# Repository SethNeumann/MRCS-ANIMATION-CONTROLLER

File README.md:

# REPO NAME: MRCS-ANIMATION-CONTROLLER
## License: Creative Commons Attribution-NonCommercial-ShareAlike

MRCS-ANIMATION-CONTROLLER

Intial use of this board is to support an animated fork lift which follows a chain with a magnet below the layout. The fork lift stops at various stations under control of diverters operated by servos. There is an on/off switch, an input for a human presence sensor, a hall effect sensore to home the chain and outputs for status LEDs.

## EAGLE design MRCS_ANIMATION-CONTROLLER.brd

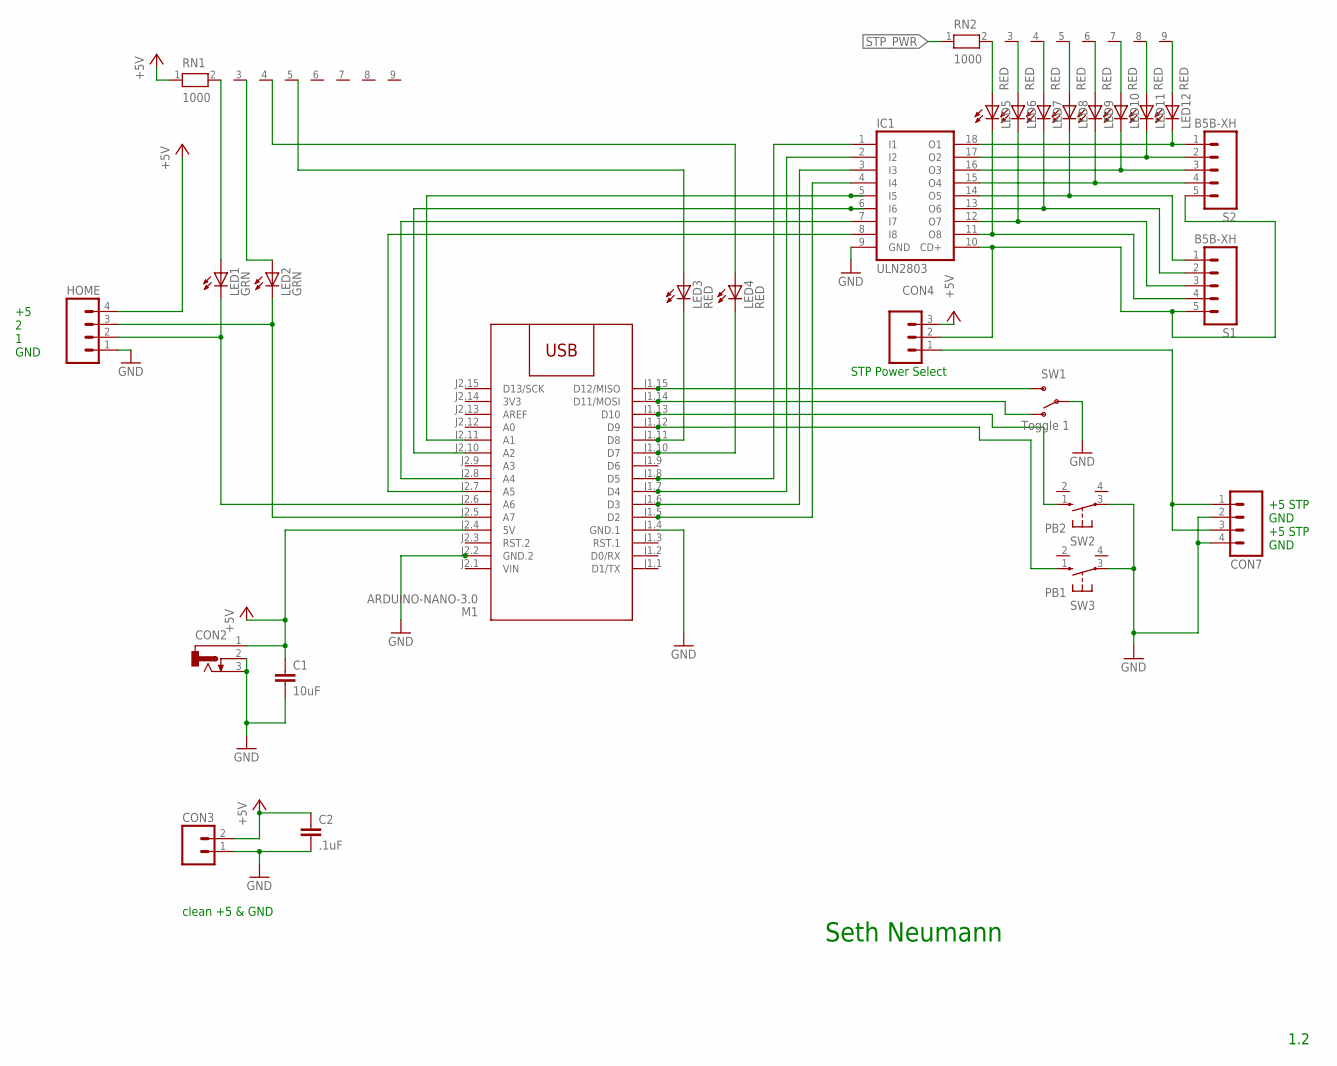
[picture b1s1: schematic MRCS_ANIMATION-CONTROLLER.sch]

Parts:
C1: 10uF; C5B3
C2: .1uF; C5B3
CON2: CONNECTOR-DC-POWER-RA; DCJ0202
CON3: CONNECTOR-M02350-LOCK; 1751248
CON4: CONNECTOR-M03254-LOCK; 3POL254
CON7: CONNECTOR-M04SCREW_LOCK; SCREWTERMINAL-3.5MM-4_LOCK
HOME: CONNECTOR-M04LOCK; 1X04_LOCK
IC1: ULN2803; DIL18
LED1, LED2: GRN; LED3MM
LED3, LED4, LED5, LED6, LED7, LED8, LED9, LED10, LED11, LED12: RED; LED3MM
M1: ARDUINO-NANO-3.0
RN1, RN2: 1000; RN-9
S1, S2: B5B-XH; 1X05_LOCK
SW1: Toggle 1; SWITCH-SPDT-508
SW2: PB2; 4P-PTH-6.0X6.0X5.0H
SW3: PB1; 4P-PTH-6.0X6.0X5.0H

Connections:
3V3: M1.J2.14 (3V3)
+5V: C1.1, C2.1, CON2.1, CON3.2 (B), CON4.3, HOME.4, M1.J2.4 (5V), RN1.1
GND: C1.2, C2.2, CON2.2, CON2.3, CON3.1 (A), CON7.2, CON7.4, HOME.1, IC1.9 (GND), M1.J1.4 (GND.1), M1.J2.2 (GND.2), SW1.2, SW2.3, SW3.3
unnamed: IC1.18 (O1), LED12.K (C), S2.1
unnamed: M1.J1.15 (D12/MISO), SW1.3 (S)
unnamed: M1.J1.14 (D11/MOSI), SW1.1 (O)
unnamed: M1.J1.13 (D10), SW2.1 (S)
unnamed: M1.J1.12 (D9), SW3.1 (S)
unnamed: LED3.K (C), M1.J1.11 (D8)
unnamed: LED4.K (C), M1.J1.10 (D7)
unnamed: LED3.A, RN1.5
unnamed: LED4.A, RN1.4
unnamed: LED2.A, RN1.3
unnamed: IC1.1 (I1), M1.J1.8 (D5)
unnamed: IC1.2 (I2), M1.J1.7 (D4)
unnamed: IC1.3 (I3), M1.J1.6 (D3)
unnamed: IC1.4 (I4), M1.J1.5 (D2)
unnamed: IC1.17 (O2), LED11.K (C), S2.2
unnamed: IC1.16 (O3), LED10.K (C), S2.3
unnamed: IC1.15 (O4), LED9.K (C), S2.4
unnamed: LED9.A, RN2.6
unnamed: HOME.3, LED2.K (C), M1.J2.5 (A7)
unnamed: LED10.A, RN2.7
unnamed: LED11.A, RN2.8
unnamed: LED12.A, RN2.9
unnamed: IC1.5 (I5), M1.J2.11 (A1)
unnamed: IC1.6 (I6), M1.J2.10 (A2)
unnamed: IC1.7 (I7), M1.J2.8 (A4)
unnamed: IC1.8 (I8), M1.J2.7 (A5)
unnamed: LED5.A, RN2.2
unnamed: CON4.1, CON7.1, CON7.3
unnamed: HOME.2, LED1.K (C), M1.J2.6 (A6)
unnamed: LED1.A, RN1.2
unnamed: LED6.A, RN2.3
unnamed: IC1.14 (O5), LED8.K (C), S1.1
unnamed: IC1.13 (O6), LED7.K (C), S1.2
unnamed: IC1.12 (O7), LED6.K (C), S1.3
unnamed: IC1.11 (O8), LED5.K (C), S1.4
unnamed: LED7.A, RN2.4
unnamed: LED8.A, RN2.5
STP_PWR: CON4.2, IC1.10 (CD+), RN2.1, S1.5, S2.5
VIN: M1.J2.1 (VIN)

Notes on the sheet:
Seth Neumann
1.2
clean +5 & GND
+5 STP GND +5 STP GND
STP Power Select
+5 2 1 GND

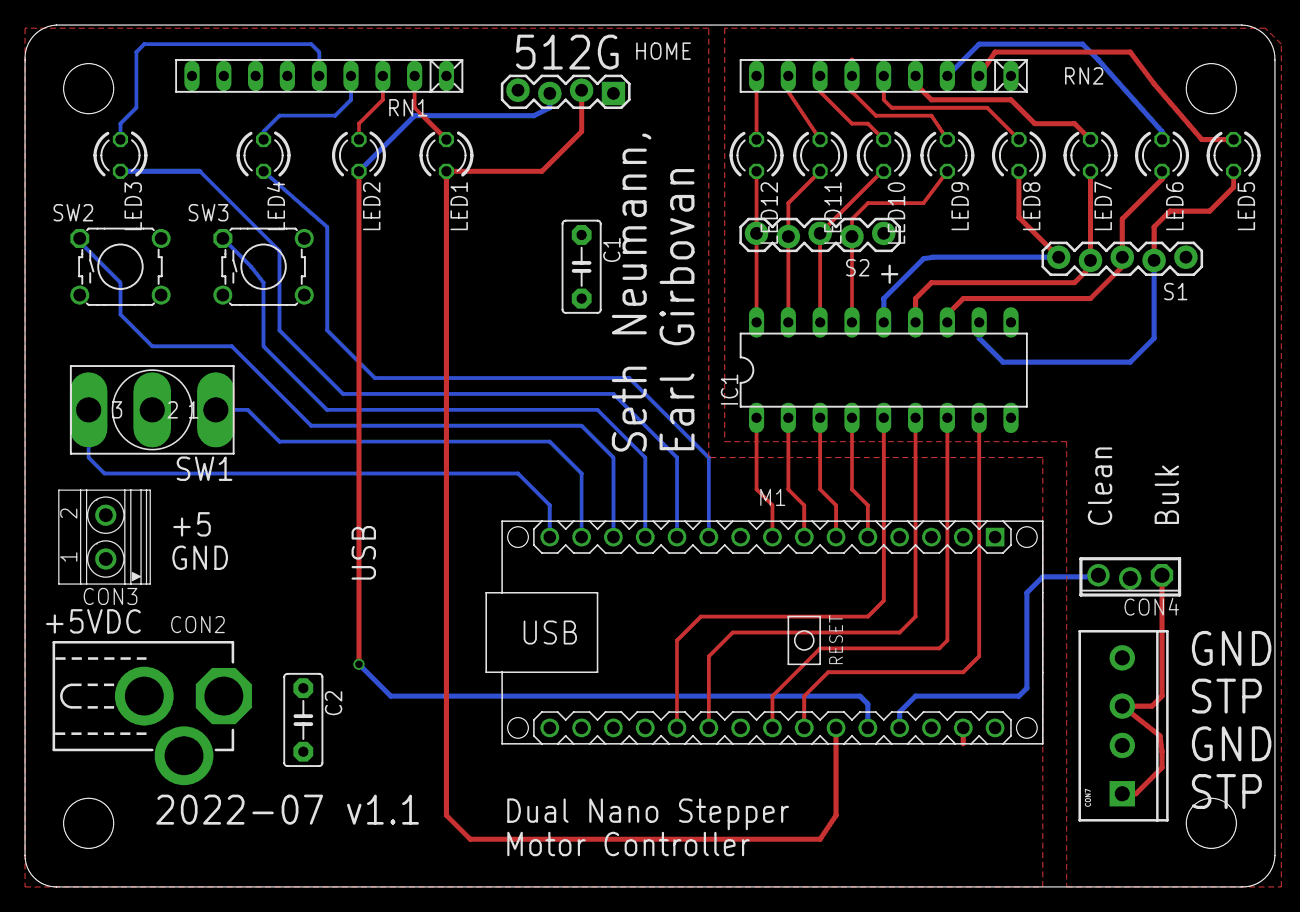
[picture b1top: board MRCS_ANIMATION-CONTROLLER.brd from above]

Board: 2 copper layers, 99.8 x 68.8 mm, 32 parts (0 on the bottom side), 40 nets.

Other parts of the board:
U$1: BOARD-DINRAIL-2.71IN-MRCS
U$2: CA-PROP65WARNING
U$3: MRCSLOGOTOP
U$4: MRCSLOGOBTM

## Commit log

2023-11-14 Update DESCRIPTION
2023-11-14 Update INFO
2023-11-14 Initial set up
    started with dual stepper motor controller

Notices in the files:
parts and their libraries:
diy-modules: Released under the Creative Commons Attribution 4.0 International License: http://creativecommons.org/licenses/by/4.0
